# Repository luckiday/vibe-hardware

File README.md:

<h1 align="center">⚡ vibe-hardware</h1>

<p align="center">
  <b>Vibe-code real hardware.</b> From a plain-language idea to working
  <b>firmware&nbsp;+&nbsp;PCB&nbsp;+&nbsp;enclosure</b> and a <b>fab order</b> — as a
  beginner — by driving an AI coding agent, not years of EDA/CAD muscle memory.
</p>

<p align="center">

</p>

<p align="center">
  <a href="docs/getting-started.md">Getting&nbsp;started</a> ·
  <a href="docs/architecture.md">Architecture</a> ·
  <a href="docs/roadmap.md">Roadmap</a> ·
  <a href="examples/">Examples</a> ·
  <a href="CONTRIBUTING.md">Contributing</a>
</p>

---

Each skill encodes the *method* and the *hard-won gotchas* for one slice of a small
embedded product — plus ready-to-run scripts and an **interactive in-browser review**,
so you never open a heavyweight GUI just to look.

> Sister project to [`earthtojake/text-to-cad`](https://github.com/earthtojake/text-to-cad)
> (whose `cad` / `cad-viewer` / `step-parts` skills these build on). vibe-hardware adds
> the **firmware → PCB → fab** half and a unified, beginner-first workflow.

## Skills

| Skill | From a spec, get… | Highlights |
|---|---|---|
| [**vibe-plm**](skills/vibe-plm/) | one manifest + interface contracts that keep the three domains in sync | `product.yaml` (identity + revision), the shared fit-number contracts, a `plm_check.py` gate, the cross-domain release checklist |
| [**vibe-firmware**](skills/vibe-firmware/) | a reproducible firmware build that flashes + runs | pinned-toolchain (Docker) builds, config-as-code, OTA, the "test on real hardware before release" rule *(framework — fill in your platform)* |
| [**vibe-uiflow**](skills/vibe-uiflow/) | a screen-and-buttons device on UIFlow2/MicroPython, in seconds per iteration | host simulator over an `M5.Lcd` stub with **device-dumped font metrics**, a bounded on-board self-test, the **ghost check**, and UIFlow2 on **non-M5 ESP32-S3 boards** |
| [**vibe-pcb**](skills/vibe-pcb/) | an ERC/DRC-clean KiCad board + a JLCPCB/LCEDA order | generate KiCad **by script** (never the GUI files), severity-aware DRC gate, module-belly keep-out, **interactive web viewer** (2D layers + 3D, one page) |
| [**vibe-cad**](skills/vibe-cad/) | a parametric build123d enclosure + STEP/STL | one parametric file, **CAD Viewer** review, board↔shell interference check (0 mm³), printability lessons |
| [**vibe-industrial-design**](skills/vibe-industrial-design/) | the product's *look*: a parametric three.js appearance model, a fixed-camera contact sheet, Blender Cycles finals, and a versioned ID/CMF report | **constraints first** — part of the form is already fixed by a spec nobody re-read, and the physics must pass through the surface you drew (ordinary plastic is opaque to LWIR); **measure the AI look image** into tagged numbers (px/mm, corner R, hole pitch, colours); **drive the image model**, don't only receive from it (`edit` refines the form, `generate` leaves it; three prompts beat three samples); one `params.js` with provenance tags, browser review + URL-driven export (raster; finals from Cycles), GLB → Blender with a **reusable hand-tuned `studio.blend`**, md-authority report + generated .docx with a change log per version |
| [**vibe-voice**](skills/vibe-voice/) | the agent *talking you through* the hands-on steps | speak the action, print the command; preflight the voice channel (a mute TTS still exits 0); poll a serial line instead of asking "did you press it?" |

`vibe-firmware` and `vibe-uiflow` are the same domain at two operating points: C/ESP-IDF
when you need determinism, power discipline and OTA; UIFlow2/MicroPython when you want the
screen to change in seconds and can trade those away. Both close the UI loop on the host.

The three domains (firmware · PCB · CAD) share **one set of fit numbers** (board outline,
stack height, mount holes, connector exits) — vibe-plm owns the contracts that hold them:
change a number once and firmware pins, board, and shell stay in sync.

**vibe-industrial-design** sits before/alongside `vibe-cad`: it decides *what the thing
looks like* (proportion, split lines, CMF, control placement) from a brief and AI look
images — which it both receives from the owner and **generates itself** from the current
render — and hands the outer numbers to the enclosure model. It starts by digging out the
constraints that already fixed part of the form, because a render that contradicts a
shipped algorithm is not a design, it's rework. `vibe-cad` decides how it holds together.

**vibe-voice** is the odd one out: not a domain, a *channel*. It turns on at the moments
the other loops hand control back to a human — flashing and probing, first power-up,
test-fitting a print — where your hands are on the hardware and nothing is left for the
keyboard.

## Install

```bash
npx skills install luckiday/vibe-hardware
```

Installs the skills into your agent (Claude Code, Codex, …). Then just ask your agent
to design the thing; it loads the relevant skill and runs the scripts. The skills also
work standalone — the `scripts/` are plain `bash`/`python`.

> The interactive viewers pull in the upstream CAD bundle:
> `npx skills install earthtojake/text-to-cad`.

## The loop (idea → fab)

```
idea ─► spec (prose) ─►  firmware   +   PCB        +   enclosure   ─► fabricate
        one brief        vibe-        vibe-pcb         vibe-cad        order board,
        per part         firmware     (KiCad, DRC)     (build123d)     print/mould shell
                                        │                      │
                                        └─ shared fit numbers ─┘
                              interactive browser review at every step (no GUI)
                              vibe-voice speaks the steps your hands are busy for
```

Start at [**docs/getting-started.md**](docs/getting-started.md).

## Examples

Worked, end-to-end builds live in [`examples/`](examples/). Flagship:

- [**pager-buddy**](examples/pager-buddy/) — a desk "pager" that lights up and buzzes on
  **Claude Code session status / notifications** (task done, waiting on input, build
  failed) and can answer prompts from the device. The **firmware** (LVGL UI + NimBLE on an
  M5StickC S3) and the **Mac bridge** (Claude Code hooks → BLE) work today; the custom
  carrier **PCB** and 3D-printed **shell** are still stubs — the in-progress target for
  vibe-pcb / vibe-cad.
- [**mic-macropad**](examples/mic-macropad/) — three MX keys and an I2S microphone on an
  ESP32-S3-WROOM-1, USB-C powered. The **board** is the finished part: contracts the
  generator never re-types, a placement laid out as a product, and a reproducible
  autoroute (a locked skeleton + an accepted freerouting session) gated at **DRC 0/0**.
  Firmware and shell are stubs. Read it for the vibe-pcb path end to end.

Add your own build as `examples/<name>/` and point the skills' "worked reference" at it.

## Philosophy

- **Beginner-first.** You bring the intent and physical constraints; the agent brings
  the EDA/CAD execution. The skills exist so a newcomer can ship a board.
- **Generate by script, review in the browser.** Sources of truth are small
  parametric/generator files (diffable, reproducible), not opaque GUI binaries — and
  you review the result interactively on `localhost`, never by booting the GUI.
- **Encode the gotchas, not just the happy path.** Every skill carries the failures
  that cost a debugging session (belly shorts, power-default-open, GLB sidecars, …).
- **Living docs.** When a real build teaches you something new, fold it back into the
  skill and commit it — compound the experience.

## Status

Early — this is the **framework**. The skills' *methods, scripts, and lessons* are real
and battle-tested. The flagship [`pager-buddy`](examples/pager-buddy/) example has working
firmware + a Mac bridge (on an M5StickC S3); its custom PCB/enclosure are still stubs.
Contributions and new examples welcome (see [CONTRIBUTING.md](CONTRIBUTING.md)).

## License

[MIT](LICENSE).

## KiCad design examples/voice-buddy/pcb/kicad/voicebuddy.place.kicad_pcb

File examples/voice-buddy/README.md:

# voice-buddy — a xiaozhi-style AI speaker, end to end

The first worked example that exercises **all four skills**: one natural-language
spec became a manifest + contracts (vibe-plm), a generated 4-layer KiCad board
(vibe-pcb; placement gated, fanout-first routing in progress), a printed 2-part
enclosure (vibe-cad), and a firmware port (vibe-firmware) for the MIT-licensed
[78/xiaozhi-esp32](https://github.com/78/xiaozhi-esp32) AI chatbot.

Hardware: ESP32-S3-WROOM-1-N16R8 · one ES8388 duplex codec (DAC → NS4150B →
rear-firing 4 Ω/3 W speaker; ADC L = analog MEMS mic, ADC R = amp echo-reference
for hardware AEC) · SSD1306 OLED on a socket · BOOT/VOL± buttons · WS2812 ·
USB-C 5 V. The audio architecture follows xiaozhi's `yunliao-s3` (ES8388 +
`AUDIO_INPUT_REFERENCE`) reference; pins are cross-checked between
`pcb/pinmap.yaml` and the firmware header by `plm_check.py`.

```
product.yaml          the manifest + interface contracts (validate: plm_check.py)
pcb/                  brief, pinmap.yaml, parts.yaml (single net source),
                      kicad/gen_sch.py + gen_pcb.py (fanout + ses replay) → board
cad/                  constraints.yaml (the shared fit numbers), voicebuddy_case.py
firmware/
  boards-port/…       drop-in board dir for upstream xiaozhi (config.h/json + class)
  selftest/           minimal ESP-IDF bring-up app (I2C scan, OLED, buttons, LED)
```

## How the language→geometry bridge works here

No coordinate in this design is hand-invented twice:

- `cad/constraints.yaml` holds every cross-domain number ONCE (outline, mount
  holes, USB-C port, panel windows, speaker). `gen_pcb.py` **reads** it — the
  board outline and connector positions are lookups, not literals.
- `pcb/parts.yaml` holds every net ONCE; the schematic and the copper both
  derive from it, so they cannot disagree.
- Placement is **relations** (`beside`, `align_pads`, `at_edge`, clusters), and
  numeric gates (courtyard/cluster overlap, keepouts, HPWL) fail the build
  before a bad floorplan reaches copper.
- Routing is **fanout-first**: `gen_pcb.py` pre-fans the plane-net pads with
  locked stubs+vias, then freerouting routes only signals (`-inc power`) and the
  accepted session (`routing.ses`) is replayed on regeneration.
- `gen_pcb.py` exports `placement.json`; `plm_check.py` compares contract vs
  evidence, and `check_fit.py` proves board↔shell interference = 0 mm³.

## Rebuild / verify

```bash
python3 ../../skills/vibe-plm/scripts/plm_check.py product.yaml     # manifest + cross-checks
cd pcb/kicad && ../../../../skills/vibe-pcb/scripts/pcb_check.sh voicebuddy   # ERC/DRC gates
cd ../../cad && ../../../.venv/bin/python build_all.py                        # enclosure
../../../.venv/bin/python ../../../skills/vibe-cad/scripts/check_fit.py voicebuddy_case.py
```

## Status — read before building one

`status: wip` on every domain. Placement gates are green and the enclosure
fit-check is 0 mm³, but **routing is still in progress — DRC is NOT yet clean**
(ERC additionally needs a ≥8 host); the firmware has **not** been compiled or
run on hardware; and datasheet values remain UNVERIFIED (ES8388 audio wiring,
NS4150B pin-1 orientation, MEMS mic port variant, AEC divider values). The
remaining routing/verification steps are tracked in `TODO.md`. Close that
checklist before ordering anything.

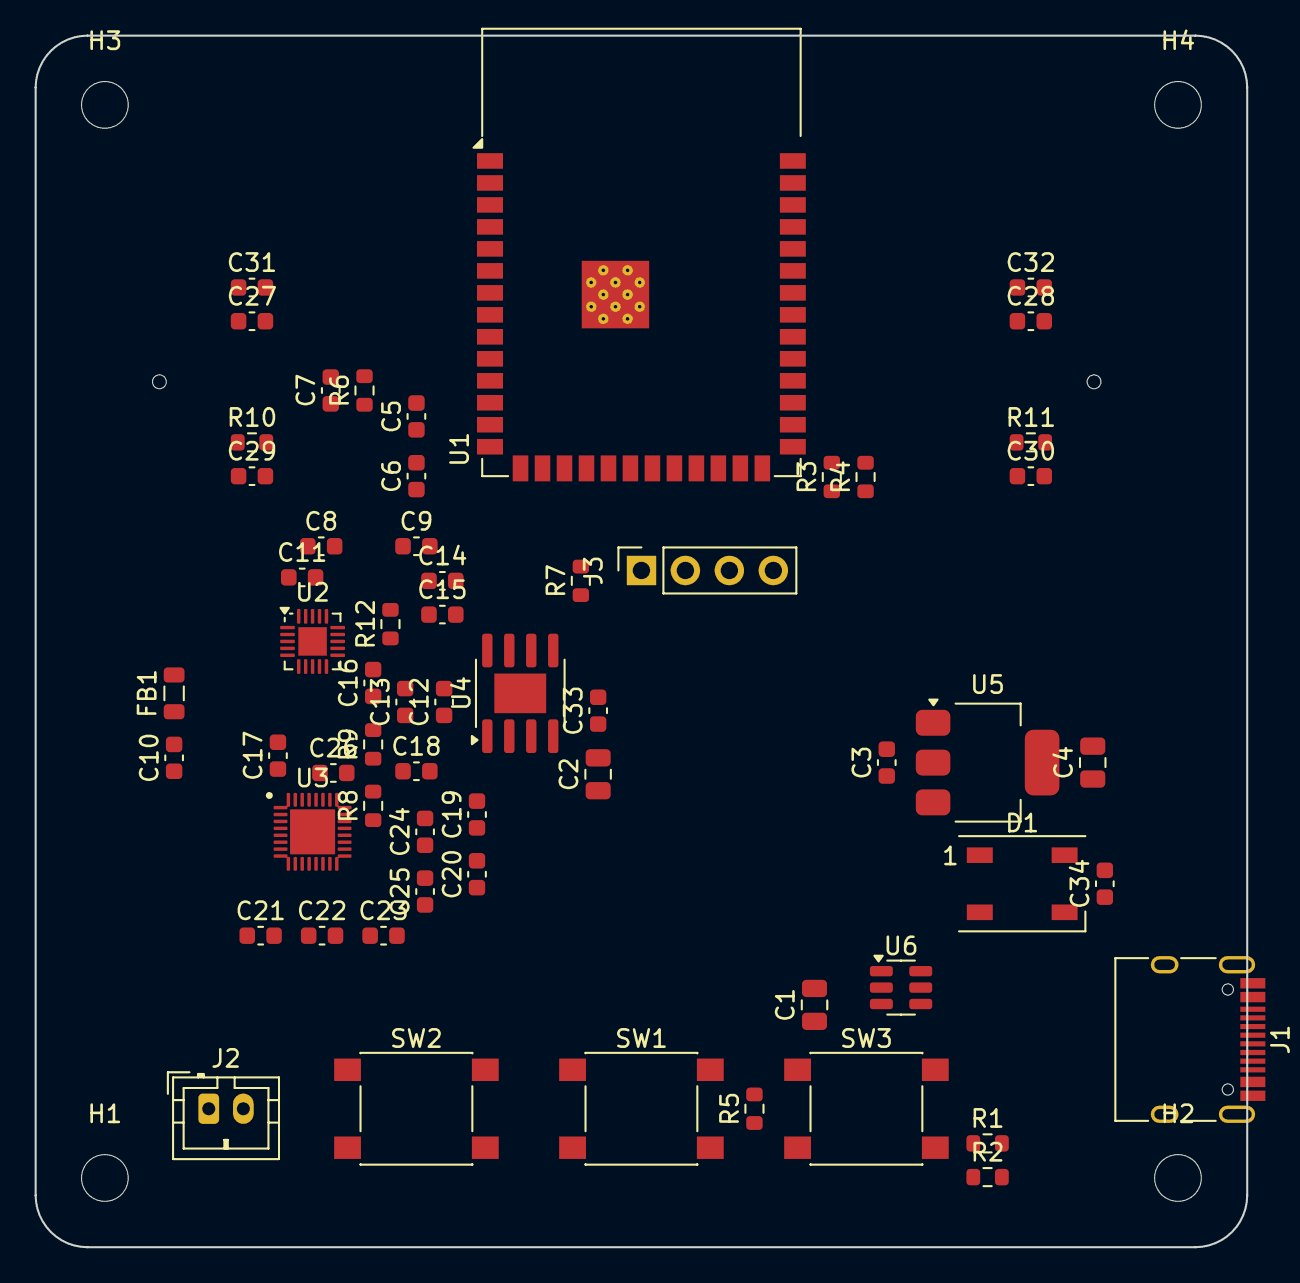
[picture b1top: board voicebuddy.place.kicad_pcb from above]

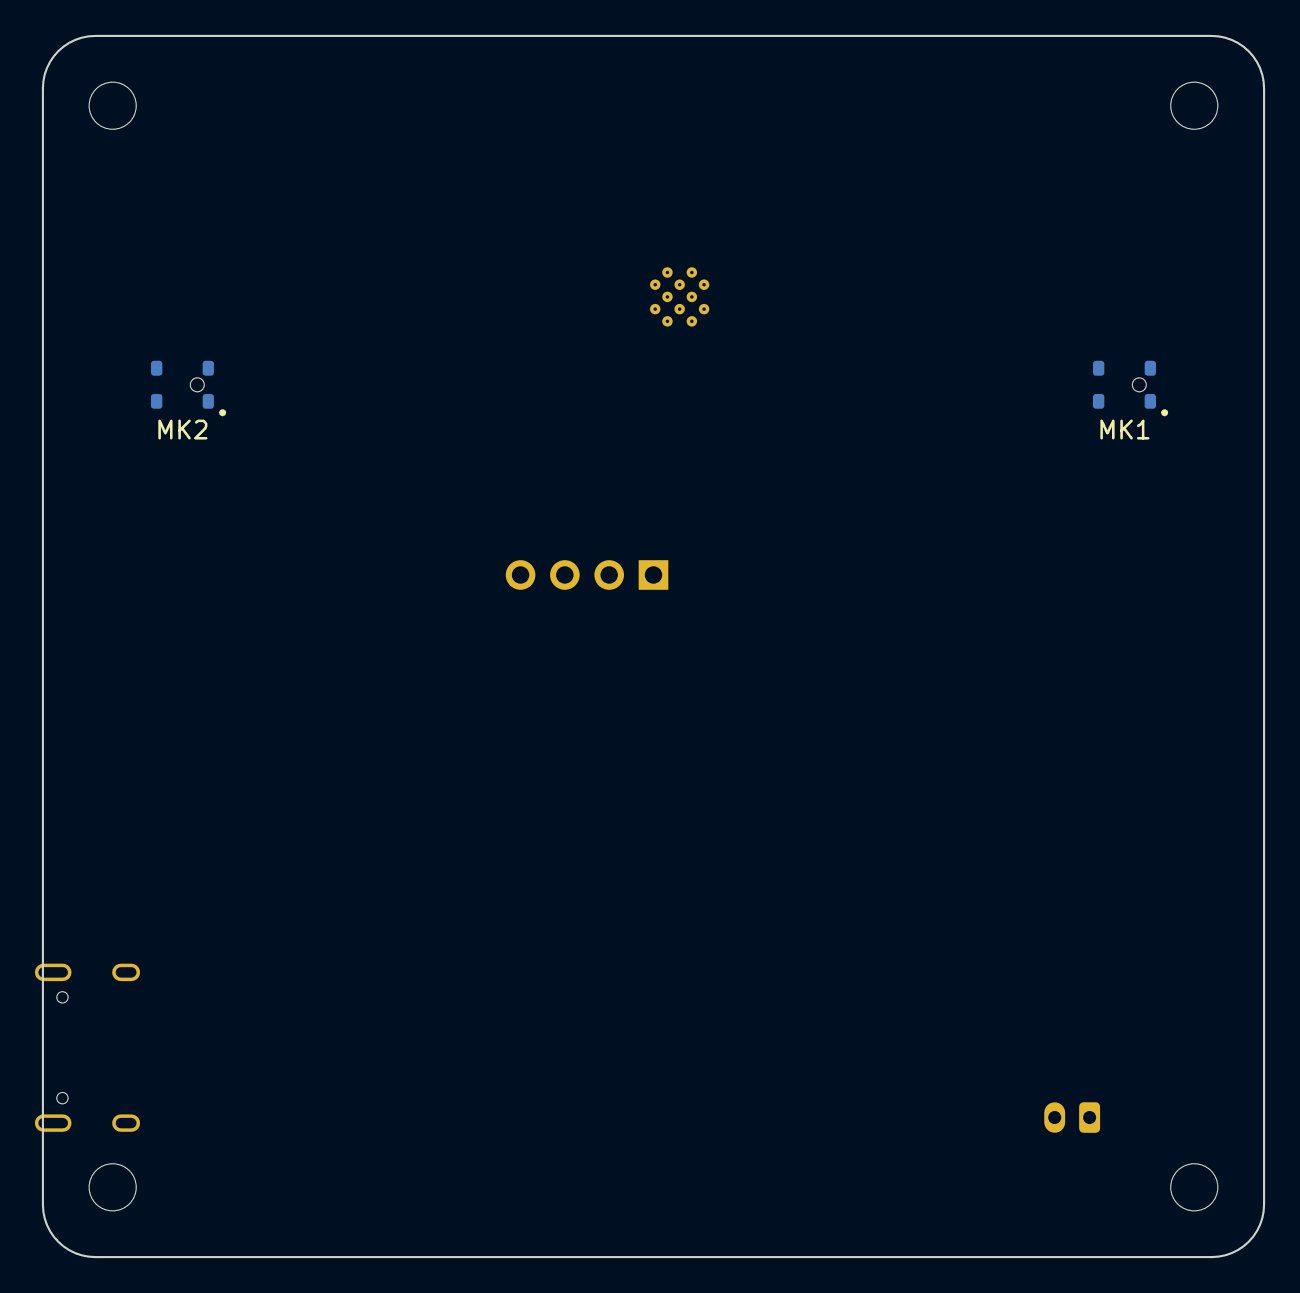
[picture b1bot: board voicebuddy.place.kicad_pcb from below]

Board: 2 copper layers, 70.0 x 70.0 mm, 66 parts (2 on the bottom side), 49 nets, no tracks yet.

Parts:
C1, C2, C4: 22u; C_0805_2012Metric
C3, C6, C10: 10u; C_0603_1608Metric
C5, C8, C9, C17, C18, C19, C20, C21, C22, C23, C25, C26, C29, C30, C31, C32, C33, C34: 100n; C_0603_1608Metric
C7, C12, C13, C14, C15, C16, C27, C28: 1u; C_0603_1608Metric
C11: 4.7u; C_0603_1608Metric
C24: 2.2u; C_0603_1608Metric
D1: WS2812B; LED_WS2812B_PLCC4_5.0x5.0mm_P3.2mm
FB1: FB 600R@100MHz; L_0805_2012Metric
H1, H2, H3, H4: MountingHole_2.7mm_M2.5
J1: USB-C-16P; USB_C_Receptacle_HRO_TYPE-C-31-M-12
J2: SPK-4ohm-3W; JST_PH_B2B-PH-K_1x02_P2.00mm_Vertical
J3: OLED-SSD1306-0.96; PinSocket_1x04_P2.54mm_Vertical
MK1, MK2: MSM381A3729; MEMS_Analog_BottomPort_3.76x2.95
R1, R2: 5.1k; R_0603_1608Metric
R3, R4, R9: 4.7k; R_0603_1608Metric
R5, R6, R12: 10k; R_0603_1608Metric
R7: 100k; R_0603_1608Metric
R8: 47k; R_0603_1608Metric
R10, R11: 100; R_0603_1608Metric
SW1: BOOT; SW_SPST_PTS645
SW2: VOL-; SW_SPST_PTS645
SW3: VOL+; SW_SPST_PTS645
U1: ESP32-S3-WROOM-1-N16R8; ESP32-S3-WROOM-1
U2: ES8311; QFN-20-1EP_3x3mm_P0.4mm_EP1.65x1.65mm
U3: ES7210; QFN-32-1EP_4x4mm_P0.4mm_EP2.6x2.6mm
U4: NS4150B; SOIC-8-1EP_3.9x4.9mm_P1.27mm_EP2.29x3mm
U5: AMS1117-3.3; SOT-223-3_TabPin2
U6: USBLC6-2SC6; SOT-23-6

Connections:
+3V3: C4.1, C5.1, C6.1, C8.1, C17.1, C34.1, D1.1, FB1.1, J3.2, R3.1, R4.1, R5.1, R6.1, U1.2, U2.3, U2.4, U3.1, U3.6, U3.7, U5.2
+3V3A: C9.1, C10.1, C18.1, FB1.2, U2.11, U3.22, U3.23
+5V: C1.1, C2.1, C3.1, C33.1, J1.A4, J1.A9, J1.B4, J1.B9, U4.6, U5.3, U6.5
AEC_IN: C16.1, R8.2, R9.1
AEC_REF: C16.2, U3.31
AMP_INN: C15.2, U4.1
AMP_INP: C14.2, U4.2
BTN_BOOT: R5.2, SW1.1, U1.27
BTN_VOLDN: SW2.1, U1.32
BTN_VOLUP: SW3.1, U1.33
CC1: J1.A5, R1.1
CC2: J1.B5, R2.1
EN: C7.1, R6.2, U1.3
ES8311_CE: R12.1, U2.20
GND: C1.2, C2.2, C3.2, C4.2, C5.2, C6.2, C7.2, C8.2, C9.2, C10.2, C11.2, C12.2, C13.2, C17.2, C18.2, C19.2, C20.2, C21.2, C22.2, C23.2, C24.2, C25.2, C26.2, C27.2, C28.2, C31.2, C32.2, C33.2, C34.2, D1.3, J1.A1, J1.A12, J1.B1, J1.B12, J1.S1, J3.1, MK1.2, MK1.4, MK2.2, MK2.4, R1.2, R2.2, R7.2, R9.2, R12.2, SW1.2, SW2.2, SW3.2, U1.1, U1.40, U1.41, U2.5, U2.10, U2.21, U3.2, U3.8, U3.21, U3.33, U4.4, U4.7, U4.9, U5.1, U6.2
I2C_SCL: J3.3, R4.2, U1.38, U2.1, U3.4
I2C_SDA: J3.4, R3.2, U1.39, U2.19, U3.3
I2S_BCLK: U1.22, U2.6, U3.9
I2S_DIN: U1.20, U3.11
I2S_DOUT: U1.26, U2.9
I2S_MCLK: U1.31, U2.2, U3.5
I2S_WS: U1.21, U2.8, U3.10
LED_DATA: D1.4, U1.25
MIC1N: C31.1, U3.15
MIC1P: C29.2, U3.16
MIC2N: C32.1, U3.20
MIC2P: C30.2, U3.19
MIC3N: C26.1, U3.32
MICBIAS12: C24.1, R10.1, R11.1, U3.24
MICBIAS34: C25.1, U3.26
MICL_OUT: C29.1, MK1.1
MICL_VDD: C27.1, MK1.3, R10.2
MICR_OUT: C30.1, MK2.1
MICR_VDD: C28.1, MK2.3, R11.2
OUTN: C15.1, U2.13
OUTP: C14.1, R8.1, U2.12
PA_EN: R7.1, U1.18, U4.3
REF12P: C19.1, U3.17
REF12Q: C20.1, U3.18
REF34P: C21.1, U3.29
REF34Q: C22.1, U3.30
REFQM: C23.1, U3.25
SPK_N: J2.2, U4.8
SPK_P: J2.1, U4.5
USB_DN: J1.A7, J1.B7, U1.13, U6.1, U6.6
USB_DP: J1.A6, J1.B6, U1.14, U6.3, U6.4
VMID: C11.1, U2.16
VREF_ADC: C13.1, U2.15
VREF_DAC: C12.1, U2.14

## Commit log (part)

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2026-06-18 chore: scaffold vibe-hardware — agent skills for vibe-coding hardware
    A public framework generalizing the firmware/PCB/CAD method from real builds, in
    the style of earthtojake/text-to-cad (skills/<name>/SKILL.md, MIT, npx-installable).
    No proprietary designs — only the general skills, scripts, and lessons.
    - README + docs/getting-started — vision, skill catalog, the idea→fab loop.
    - skills/text-to-pcb — spec→KiCad-by-script→DRC-clean→fab + the unified browser
    viewer (2D layers | 3D | Split); scripts: pcb_check / pcb_view / fab_export / belly_check.
2026-06-18 refactor: rename skills text-to-* → vibe-*; add AGENTS.md + CLAUDE.md
    - skills/text-to-{pcb,cad,firmware} → skills/vibe-{pcb,cad,firmware} (git mv) and
    every cross-reference updated, preserving the UPSTREAM earthtojake/text-to-cad refs.
    - AGENTS.md — agent guidance for this repo (repo map, repo rules: skills self-
    contained / generate-by-script-review-in-browser / generic-designs-only / living
    docs, environments, checks, git, always-never), adapted from the reference repo.
    - CLAUDE.md — imports AGENTS.md (@AGENTS.md).
2026-06-18 docs: all-English copy — "BP机" → pager, translate Chinese EDA/fab terms
    Public repo should be English-only. Replaced the pager nickname and the
    Chinese terms carried over from the private references:
    - 立创EDA → EasyEDA (LCEDA); 立创 → LCSC / JLCPCB per context
    - 网表不一致 → "netlist mismatch"; 元件…缺少"封装"属性 → component … missing
    "footprint" property; 缺少封装 → "missing footprint"
2026-06-18 chore: repo scaffolding + docs + README presentation
    - LICENSE copyright -> @luckiday.
    - Scaffolding (learned from the reference repo): .github CI (skill-structure +
    py-compile + English-only guard + advisory shellcheck), issue/PR templates,
    requirements.txt, CHANGELOG.md, .editorconfig, CODE_OF_CONDUCT.md, assets/.
    - docs/: architecture.md (mental model, repo layout, skill anatomy, data flow),
    roadmap.md (phased living plan), README index.
2026-06-23 feat(vibe-pcb): headless freerouting autoroute recipe + scripts
    The skill claimed "freerouting runs headless" in one line; this fills in the
    validated, fully-headless recipe and the non-obvious gotchas found building a real
    module-carrier (autorouted board matched the hand-routed one: DRC 0/0/0,
    0 unconnected, belly PASS, power 0.4 / signal 0.3 mm).
    - references/autorouting.md: pipeline (gen STAGE=place -> export_dsn -> freerouting
    -> import_ses -> pcb_check) sitting between P4 and P6, plus 6 gotchas:
